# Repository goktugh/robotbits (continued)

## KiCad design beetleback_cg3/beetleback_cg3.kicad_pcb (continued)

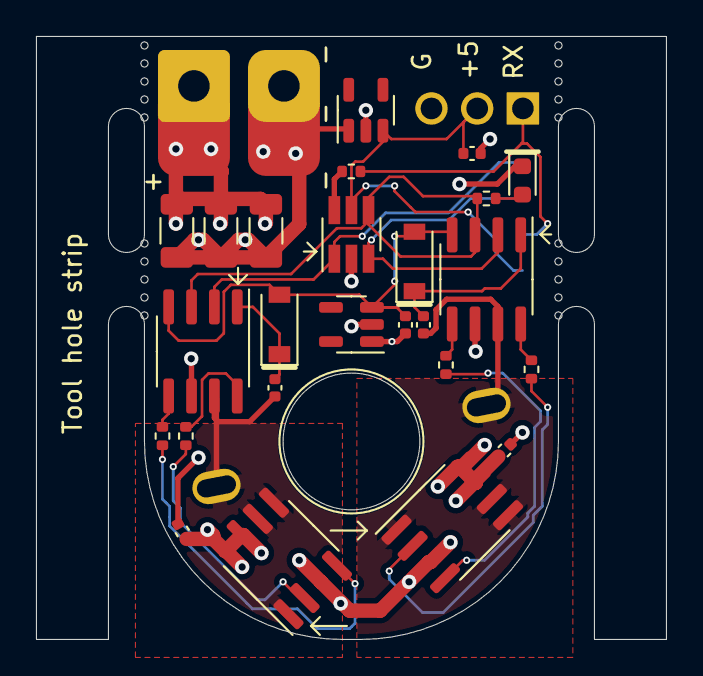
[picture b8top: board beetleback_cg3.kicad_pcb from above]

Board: 4 copper layers, 35.0 x 33.5 mm, 30 parts (1 on the bottom side), 22 nets.

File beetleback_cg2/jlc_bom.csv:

Comment,Designator,Footprint,LCSC
ATtiny13A-SS,"U1",Package_SO:SOIC-8_3.9x4.9mm_P1.27mm,C14075
HT7550-2,"U3",Package_TO_SOT_SMD:SOT-23-5,C81799
22uF 25v,"C5,C6,C7",Capacitor_SMD:C_1206_3216Metric,C12891
IRF8313PBF,"Q2,Q1",Package_SO:SOIC-8_3.9x4.9mm_P1.27mm,C57696
HT75C0-2,"U5",Package_TO_SOT_SMD:SOT-23-5,C95005
10R,"R5,R6,R3,R2",Resistor_SMD:R_0402_1005Metric,C25077
1uF 25v,"C1,C2,C4,C9,C3,C8",Capacitor_SMD:C_0402_1005Metric,C52923
B5819W,"D1,D3",Diode_SMD:D_SOD-123,C8598
ADP3110A,"U2,U4",Package_SO:SOIC-8_3.9x4.9mm_P1.27mm,C82321
1k,"R1,R4",Resistor_SMD:R_0402_1005Metric,C11702
Red LED,"D2",LED_SMD:LED_0603_1608Metric,C2286

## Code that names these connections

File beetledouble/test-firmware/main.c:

#include <avr/io.h>

#define F_CPU 20000000 /* 20MHz / prescale=1 */
#include <util/delay.h>

#include <string.h>
#include <stdarg.h>
#include <stdio.h>
#include <stdbool.h>

#include "diag.h"

static void init_clock()
{
    // This is where we change the cpu clock if required.
    // uint8_t val = CLKCTRL_PDIV_2X_gc | 0x1;  // 0x1 = PEN enable prescaler.
    uint8_t val = 0;  // 0 = no prescaler, full speed.
    _PROTECTED_WRITE(CLKCTRL.MCLKCTRLB, val);
    _delay_ms(10);
}

static void init_serial()
{
    // UART0- need to use "alternate" pins 
    // This puts TxD and RxD on PA1 and PA2
    PORTMUX.CTRLB = PORTMUX_USART0_ALTERNATE_gc; 
    // Diagnostic uart output       
    // TxD pin PA1 is used for diag, should be an output
    // And set it initially high
    PORTA.OUTSET = 1 << 1;
    PORTA.DIRSET = 1 << 1;
    
    uint32_t want_baud_hz = 230400; // Baud rate (was 115200)
    uint32_t clk_per_hz = F_CPU; // CLK_PER after prescaler in hz
    uint16_t baud_param = (64 * clk_per_hz) / (16 * want_baud_hz);
    USART0.BAUD = baud_param;
    USART0.CTRLB = 
        USART_TXEN_bm | USART_RXEN_bm; // Start Transmitter and receiver
    // Enable interrupts from the usart rx
    // USART0.CTRLA |= USART_RXCIE_bm;
}

/*
 * Ports to test as output:
 * 
 * PA4,5,6,7
 * PB0,1 (NOT PB2 which is GNDSHUNT)
 */

static uint8_t bm_a = 0xf0; // 4,5,6,7
static uint8_t bm_b = 0x03; // 0,1;

static void all_outputs_low()
{
    PORTA.OUTCLR = bm_a;
    PORTA.DIRSET = bm_a;
    PORTB.OUTCLR = bm_b;
    PORTB.DIRSET = bm_b; 
}

// Make all output pins inputs, if that even makes sense?
static void all_pins_in()
{
    PORTA.DIRCLR = bm_a;
    PORTB.DIRCLR = bm_b; 
}

static void dump_port(PORT_t * port, char portname) {
    diag_print("INPUTS FOR PORT %c: ", portname);
    uint8_t value = port->IN; // read port
    for (int8_t i=7; i>=0; --i) {
        diag_print("%d", (value << i) & 1); 
    }
    diag_puts("\r\n");
}
static void dump_ports()
{
    dump_port(&PORTA, 'A');
    dump_port(&PORTB, 'B');
}

static void test_pin(PORT_t *port, char portname, uint8_t pin) 
{
    diag_println("Testing PORT %c PIN %d", portname, pin);
    all_outputs_low();
    _delay_ms(50);
    all_pins_in();
    // Set the pin low
    port->DIRSET = 1 << pin;
    _delay_ms(10);
    dump_ports();
    // Set the pin high
    port->OUTSET = 1 << pin;
    _delay_ms(10);
    dump_ports();
    diag_println("Done");
    all_pins_in();
}


static void test_pin_shorts()
{
    for (uint8_t i=4; i<8; i++) {
        test_pin(&PORTA, 'A', i);
    }
    for (uint8_t i=0; i<2; i++) {
        test_pin(&PORTB, 'B', i);
    }
}

static void go_to_sleep()
{
    // Ultra low power 32k internal oscilator
    uint8_t val = 0x1; // OSCULP32K
    _PROTECTED_WRITE(CLKCTRL.MCLKCTRLA, val);
    // Foreer loop
    for ( ;; );
    
}

int main(void)
{
    init_clock();
    init_serial();
    diag_puts("\n\nTest firmware starting\r\n");
    test_pin_shorts();
    go_to_sleep();
}

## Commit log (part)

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2018-08-26 update control scheme for faster motors, better control
2018-08-26 more pid tweaks
2018-08-28 cutout bit for these shafts
2018-08-28 control updates
2018-09-04 armour 3d fudge
2018-10-01 detect bad json from imu
2018-10-11 auto retract flipper while driving
2018-10-12 Special retract mode; systemd for pigpiod
2018-10-15 experiments
2018-10-15 imu_daemon reset mpu if it goes wonky
2018-10-19 imu_daemon fix silly bug
2018-10-21 record driving data
2018-10-22 Stronger flipper; previous base changes for Betsie
2018-11-11 PCB for Betsie flipper and power
2018-11-26 nrfbot blinky test program even though it does not work
2018-12-01 blender seal
2018-12-02 flip motor mount; blender seal
2019-01-14 new flipper controll gpios and various updates
2019-01-14 remove misleading doc
2019-01-14 flipper timing
2019-01-17 new flip motor mount
2019-01-18 fixing flipper to be stronger etc
2019-01-25 Armour updates
2019-01-25 fix for getting the armour weight cutouts right
2019-01-29 Swap flipper gpios
2019-01-31 various improvements; record data only when tx on
2019-04-10 New robot shell
2019-04-12 Stacie some more hardware
2019-04-13 more wheels and gears
2019-04-25 stacie2: hardware tweaks
2019-04-27 misc changes
2019-05-03 Many updates
2019-05-05 2d version of idle gear for lasercut
2019-05-09 splodge factor in gears and other changes
2019-05-25 Design tweaks for stacie
2019-05-27 more small tweaks
2019-06-02 build
2019-06-04 switch from gears to pulleys
2019-06-09 move to 4-wd; flip lid
2019-06-10 new side bracket thing to strengthen it
2019-06-13 Big Stacie redesign
2019-06-13 Tyre mould for much smaller tyres
2019-06-14 misc bits
2019-06-16 Flip coupler update
2019-06-22 Flip coupler: Add more tolerance on shaft hole
2019-06-26 tyre mould better thickness
2019-07-03 Cube update
2019-07-16 Betsie boost board
2019-10-03 Penelope info
2019-11-10 thicker tyre
2019-11-17 Script to automate install of toolchain
2019-11-28 lid, drive belt etc
2020-01-15 space for the hex flip coupler
2020-01-15 add the old flip coupler, it is still useful
2020-01-16 tolerance for hex size
2020-01-22 gpio test program
2020-01-22 Send a serial string to each gpio port so we can identify them and make sure they are all working
2020-02-25 gpiohello prog bits
2020-02-25 a7105 module reverse engineered and rebuilt
2020-03-07 the reverse engineered module
2020-03-07 This was an update to add a ceramic cap to the output because those tants do not work well. but I did not respin the board I just hacked it
2020-03-07 show device info
2020-03-19 Somewhat interesting assembly example
2020-05-07 Erm, a thingy
2020-05-07 is it a beetle esc?
2020-05-07 maybe a beetle esc
2020-05-07 is it a thing?
2020-05-12 latest
2020-05-22 various pcb designs
2020-05-26 Another crazy version of rx
2020-06-13 Shiny thing
2020-06-13 Shiny thing lcsc parts and fixes
2020-07-19 first version of melty controller
2020-07-21 switcharoo power to bigger dual ldo regulators
2020-07-21 clean up net names and stuff
2020-07-21 Fix Antenna footprint; use zener to regulate 5.0v
2020-07-21 Use real regulator for 5.0 and tidy up schematic
2020-07-21 Schematic updates; assign lcsc part numbers
2020-07-24 esp32 more playing
2020-07-26 more esp32 fun
2020-07-27 update bom
2020-08-01 a version using a different radio module
2020-08-01 A version of Malenki-nano with radio included on board
2020-08-02 Maybe different pcb
2020-08-02 Fun experiment!
2020-08-02 Shiny thing schematic in convenient pdf
2020-08-08 Add more testpoints and minor fixes
2020-08-09 Update to pcb tweaks e.g. silkscreen
2020-08-15 A7105 module experiments
2020-08-15 some hardware ideas for stacie the robot
2020-08-15 old design for a beetleweight esc
2020-08-16 dshot motors driver
2020-08-18 wifi password in uncommitted file; other stuff
2020-08-24 more work on the melty
2020-08-25 more tweaks
2020-08-27 Meltybrain firmware stuff
2020-08-29 Get telemetry going from esc
2020-09-01 Motors telemetry stuff
2020-09-05 Better shell
2020-09-06 motorback idea
2020-09-06 update of shell
2020-09-14 The melty hardware
2020-09-16 Get the hole spacing correct
2020-09-17 wheel to fit over the 1104 brushless motor
2020-10-08 motorback update lcsc part numbers
2020-10-21 correct some doc errors on schematic
2020-10-21 new 2-layer version of melty controller
2020-10-21 melty controller 2
2020-10-22 bendy version of the controller
2020-11-01 Melty design bits
2020-11-02 shell: updates, screw holes etc
2020-11-05 beetle motor esc back
2020-11-06 board update
2020-11-17 fixes
2020-11-20 crc check motor telemetry
2020-11-29 melty controller: controller stuff for ps3 or ps4 controller
2020-12-03 Add PS3 controller support to the firmare
2020-12-03 motor drive spinup with both motors, telemetry fix etc
2020-12-09 client program
2020-12-13 Use double sided jst; add bbb logo
2020-12-14 minor fixes
2020-12-15 Use 4-layer board
2020-12-15 identify correct parts, update schematic
2020-12-15 Correct schematic booboo: use n-channel mosfets instead of a mixture
2020-12-16 Beetleback minor update and ordered
2020-12-17 Attiny13a program
2020-12-19 Testing the attiny13 more
2020-12-20 diagram of relative positions of stuff
2020-12-26 4-layer Malenki-nano
2020-12-27 Crystal caps update
2020-12-27 Use hand-solder footprints for all 0402
2020-12-28 update some comments pin1 marks on silkscreen
2020-12-28 Change crystal
2020-12-28 Assign manufacturer part numbers and lcsc numbers
2020-12-29 remove unused files
2021-01-01 update to linear regulator
2021-01-01 misc update
2021-01-01 dimension fixes
2021-01-01 dimension fixes and move cap
2021-01-01 mod soic8 footprint, minor updates
2021-01-03 panels tweak
2021-01-04 use some 0402 caps; fix missing route from led resistor
2021-01-05 version with sot23-6 microcontroller
2021-01-05 tweaks
2021-01-07 tiny4 test
2021-01-08 Enable good assembly output
2021-01-08 Tiny microcontroller experiments
2021-01-10 More tweaks, use 3-way connector fix 3d models
2021-01-11 Firmware first try
2021-01-14 motorback more compact layout
2021-01-17 new revision
2021-01-17 mechanical improvements
2021-01-17 Antweight cube
2021-01-19 Correct tpiclk / tpidata confusion
2021-01-19 minor fixups
2021-01-20 programmer
2021-01-20 Optional pull-down resistor
2021-01-21 Fix: NSLEEP must not be powered from regulator
2021-01-21 remove unnecessary bits
2021-01-21 paneling again
2021-01-23 test of attiny13 - continued
2021-01-23 reorganisation
2021-01-23 remove old files
2021-01-23 firmware for motorback;
2021-01-24 Optional 5v regulator for RX
2021-01-25 firmware tweak
2021-01-27 Beetleback firmware
2021-01-27 Beetleback firmware: Partially working version perhaps
2021-01-29 Rev2 hardware: update mosfet, silkscreen tweaks, lcsc part numbers
2021-01-30 Increase dead zone and ignore spurious pulses
2021-02-10 Make pwm work correctly
2021-02-10 Use 1k resistors
2021-02-15 Beetleweight triple esc
2021-02-15 Beetleweight triple: redo the power and passives
2021-02-15 Beetleweight triple: more.
2021-02-16 Pin swaps and routing
2021-02-17 misc updates
2021-02-17 Shunt current sensor. Many improvements, layout updates
2021-02-18 add lcsc part numbers
2021-02-18 Footprint improvements
2021-02-18 Beetletriple version x1 with the dfn-8 gate driver
2021-02-19 Add gate resistors; re-layout
2021-02-20 Complete routing latest variation
2021-02-23 Footprints shenanigans
2021-02-23 Add another capacitor on 12v line
2021-02-25 minor updates
2021-03-01 N20 firmware tweak
2021-03-06 Latest tweaks
2021-03-07 Slighty bigger motor holes; slightly smaller vias
2021-03-07 Panel of 4, as made for prototypes
2021-03-07 Notes
2021-03-16 Minor updates: drv8837d footprint tweak
2021-03-24 Panel of 16 as sent to fab
2021-03-25 ASsembly diagram
2021-03-25 freecad hardware
2021-03-26 fixups
2021-04-20 firmware shenanigans
2021-04-23 Configurable mcu option to prog_loop
2021-04-25 control and telemetry
2021-04-27 lcsc scraper
2021-05-03 Beetleweight dual esc
2021-05-03 Beetle double driver update with differen fets
2021-05-03 Melty firmware
2021-05-09 N20 red esc - documentation
2021-05-14 beetledouble esc wip
2021-05-17 Beetle esc
2021-05-20 Beetleweight power distribution board
2021-05-23 Gears shenanigans
2021-05-23 Stacie: strengthen flip coupler
2021-05-26 a8105 test pcb
2021-06-05 Beetledouble ESC
2021-06-05 A8105 radio mcu test
2021-06-05 special footprints for pth+smd
2021-06-25 Beetlepower-rightangle
2021-06-26 Beetlepower right angle board
2021-06-28 Another version of Beetlepower RA with cable tie slots
2021-07-09 lawnmower
2021-07-14 corner bracket
2021-07-21 update design bits
2021-07-23 back panel
2021-07-24 thinner gear
2021-07-25 flipgear update
2021-07-26 Move the set-screw location
2021-07-27 Improve battery holder
2021-07-29 lidgear update
2021-07-30 lidgear tweak teeth again
2021-07-30 13 teeth is the magic number
2021-07-31 lid gear reduce slightly and also expand holes for threaded inserts
2021-08-02 Beetleback, Chipageddon edition
2021-08-02 Tool hole strip
2021-08-02 lid gear smaller holes for threaded inserts and other mods
2021-08-05 stuff
2021-08-06 another beetleback esc layout
2021-08-06 remove files
2021-08-06 edge rails
2021-08-23 fix capcitor lcsc id, change driver chip to NCP81155
2021-08-23 Impostor
2021-09-13 motor mount
2021-09-16 model of radio module
2021-09-25 Firmware testimage
2021-09-26 Beetledouble firmware test
2021-09-26 Beetledouble hardware (reogranisation)
2021-09-26 Beetledouble: restructure
2021-09-27 Lawnmower stuff
2021-09-28 esc firmware
2021-10-02 Motor driver firmware update
2021-10-03 Beetledouble firmware update
2021-10-05 Update toolchain with latest patch
2021-10-06 try to design a buck regulator board
2021-10-06 update pcb
2021-10-06 some ideas from a while ago
2021-10-06 old ideas
2021-10-06 power distribution board
2021-10-06 Minor pcb tweaks for better reliability solderability etc
2021-10-08 Hardware misc updates
2021-10-09 Test firmware
2021-10-09 Firmware tweaks
2021-10-10 Pin updates to get ADC pins and VSENSE and ISENSE etc
2021-10-12 slightly shrink
2021-10-12 shrink board slightly
2021-10-13 lcsc ids and comments and stuff
2021-10-13 Code to query the config pad on the same pin as txdebug
2021-10-14 Misc tidyups
2021-10-18 Initial hack at overcurrent protection
2021-10-18 overcurrent protection
2021-10-19 set low side during overcurrent recovery
2021-10-24 Resistor to smooth out mcu power slightly
2021-10-27 MCU power fixup
2021-10-27 Update regulator footprint; silkscreen fixes
2021-11-05 Current sensing stuff
2021-11-06 lcsc scraping stuff
2021-11-14 Minor tweaks 15ohm resistor for gates
2021-11-14 Graphics
2021-11-15 Replace zener with ht7550-2 sot23-5 reg
2021-11-20 FeatherESC power board
2021-11-20 Remove obsoolete files
2021-11-21 Featheresc ideas
2021-11-22 hardware bits
2021-11-22 Featheresc logic
2021-11-26 Power board: update terminals, many minor tweaks
2021-11-28 Laser cut testrig
2021-12-01 New version with the attiny4-ma
2021-12-01 Panel of 20 red esc
2021-12-01 Red esc 2022 edition
2021-12-10 Panel script for red esc
2021-12-10 redesc git tidy up
2021-12-10 experiments in feather esc
2021-12-12 More ideas for feather esc
2021-12-14 feather power
2021-12-15 Silkscreen etc
2021-12-15 power minor tweaks
2021-12-16 Rev3 firmware
2021-12-17 improve interconnect pinouts
2021-12-18 Mixing switch
2021-12-18 Improve 3d model
2021-12-20 Diag bitbang; improve vsense
2021-12-23 Prepare for configmode
2021-12-23 Config mode menu
2021-12-27 Config mode largely implemented
2021-12-28 Config mode: fix stupid bug in configvars.c setting defaults
2021-12-28 Config mode: fix more issues; implement vsense for 3s
2021-12-28 Update todo
2021-12-30 isense: fixups; rxin: lower tolerance of electrical noise to avoid unintended movement
2021-12-30 Startup beep
2021-12-30 Pulldown EN pins
2022-01-02 Featheresc logic: add more decoupling caps etc
2022-01-02 Vsense: detect 4S pack or higher
2022-01-04 motor mount tweaks
2022-01-06 Vacuum cleaner shim
2022-01-24 Recharge capacitors less often
2022-01-29 Mixing first implementation
2022-01-30 Mixing: respect config vars including braking
2022-01-30 Ensure motors are off on undervoltage
2022-01-31 Cosmetic
2022-02-20 Usb serial thing
